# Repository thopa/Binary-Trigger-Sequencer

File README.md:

# Binary-Trigger-Sequencer
8 Channel Eurorack Binary Trigger Sequencer

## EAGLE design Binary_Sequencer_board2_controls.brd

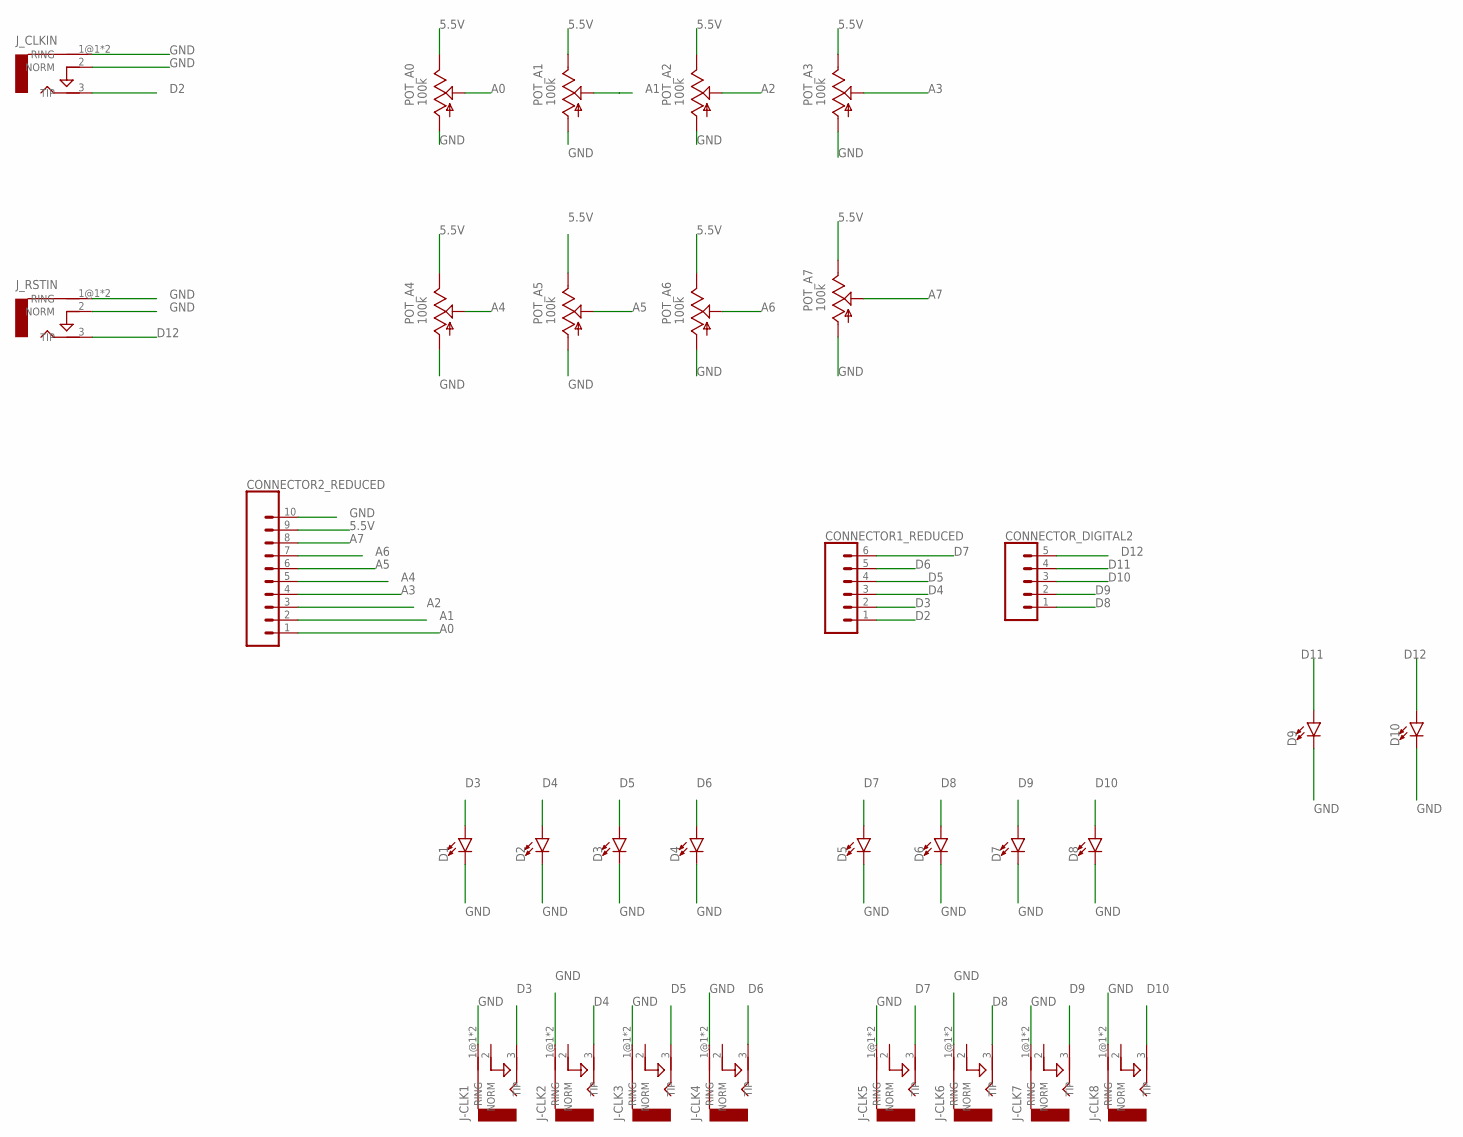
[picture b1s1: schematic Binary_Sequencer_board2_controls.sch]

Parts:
CONNECTOR1_REDUCED: CONN_06LONGPADS; 1X06_LONGPADS
CONNECTOR2_REDUCED: CONN_10_LONGPADS10_LONGPADS; 1X10_LONGPADS
CONNECTOR_DIGITAL2: CONN_05PTH_LONGPADS; 1X05_LONGPADS
D1, D2, D3, D4, D5, D6, D7, D8, D9, D10: LED-3MM-NO_SILK; LED_3MM-NS
J-CLK1, J-CLK2, J-CLK3, J-CLK4, J-CLK5, J-CLK6, J-CLK7, J-CLK8: AUDIO-JACKERTHENVAR; ERTHENVAR-JACK
J_CLKIN: AUDIO-JACKERTHENVAR; ERTHENVAR-JACK
J_RSTIN: AUDIO-JACKERTHENVAR; ERTHENVAR-JACK
POT_A0, POT_A1, POT_A2, POT_A3, POT_A4, POT_A5, POT_A6, POT_A7: 100k; 9MM_SNAP-IN_POT

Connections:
5.5V: CONNECTOR2_REDUCED.9, POT_A0.3 (E), POT_A1.3 (E), POT_A2.3 (E), POT_A3.3 (E), POT_A4.3 (E), POT_A5.3 (E), POT_A6.3 (E), POT_A7.3 (E)
A0: CONNECTOR2_REDUCED.1, POT_A0.2 (S)
A1: CONNECTOR2_REDUCED.2, POT_A1.2 (S)
A2: CONNECTOR2_REDUCED.3, POT_A2.2 (S)
A3: CONNECTOR2_REDUCED.4, POT_A3.2 (S)
A4: CONNECTOR2_REDUCED.5, POT_A4.2 (S)
A5: CONNECTOR2_REDUCED.6, POT_A5.2 (S)
A6: CONNECTOR2_REDUCED.7, POT_A6.2 (S)
A7: CONNECTOR2_REDUCED.8, POT_A7.2 (S)
D2: CONNECTOR1_REDUCED.1, J_CLKIN.3 (TIP)
D3: CONNECTOR1_REDUCED.2, D1.A, J-CLK1.3 (TIP)
D4: CONNECTOR1_REDUCED.3, D2.A, J-CLK2.3 (TIP)
D5: CONNECTOR1_REDUCED.4, D3.A, J-CLK3.3 (TIP)
D6: CONNECTOR1_REDUCED.5, D4.A, J-CLK4.3 (TIP)
D7: CONNECTOR1_REDUCED.6, D5.A, J-CLK5.3 (TIP)
D8: CONNECTOR_DIGITAL2.1, D6.A, J-CLK6.3 (TIP)
D9: CONNECTOR_DIGITAL2.2, D7.A, J-CLK7.3 (TIP)
D10: CONNECTOR_DIGITAL2.3, D8.A, J-CLK8.3 (TIP)
D11: CONNECTOR_DIGITAL2.4, D9.A
D12: CONNECTOR_DIGITAL2.5, D10.A, J_RSTIN.3 (TIP)
GND: CONNECTOR2_REDUCED.10, D1.K (C), D2.K (C), D3.K (C), D4.K (C), D5.K (C), D6.K (C), D7.K (C), D8.K (C), D9.K (C), D10.K (C), J-CLK1.1@1 (RING), J-CLK1.1@2 (RING), J-CLK2.1@1 (RING), J-CLK2.1@2 (RING), J-CLK3.1@1 (RING), J-CLK3.1@2 (RING), J-CLK4.1@1 (RING), J-CLK4.1@2 (RING), J-CLK5.1@1 (RING), J-CLK5.1@2 (RING), J-CLK6.1@1 (RING), J-CLK6.1@2 (RING), J-CLK7.1@1 (RING), J-CLK7.1@2 (RING), J-CLK8.1@1 (RING), J-CLK8.1@2 (RING), J_CLKIN.1@1 (RING), J_CLKIN.1@2 (RING), J_CLKIN.2 (NORM), J_RSTIN.1@1 (RING), J_RSTIN.1@2 (RING), J_RSTIN.2 (NORM), POT_A0.1 (A), POT_A1.1 (A), POT_A2.1 (A), POT_A3.1 (A), POT_A4.1 (A), POT_A5.1 (A), POT_A6.1 (A), POT_A7.1 (A)

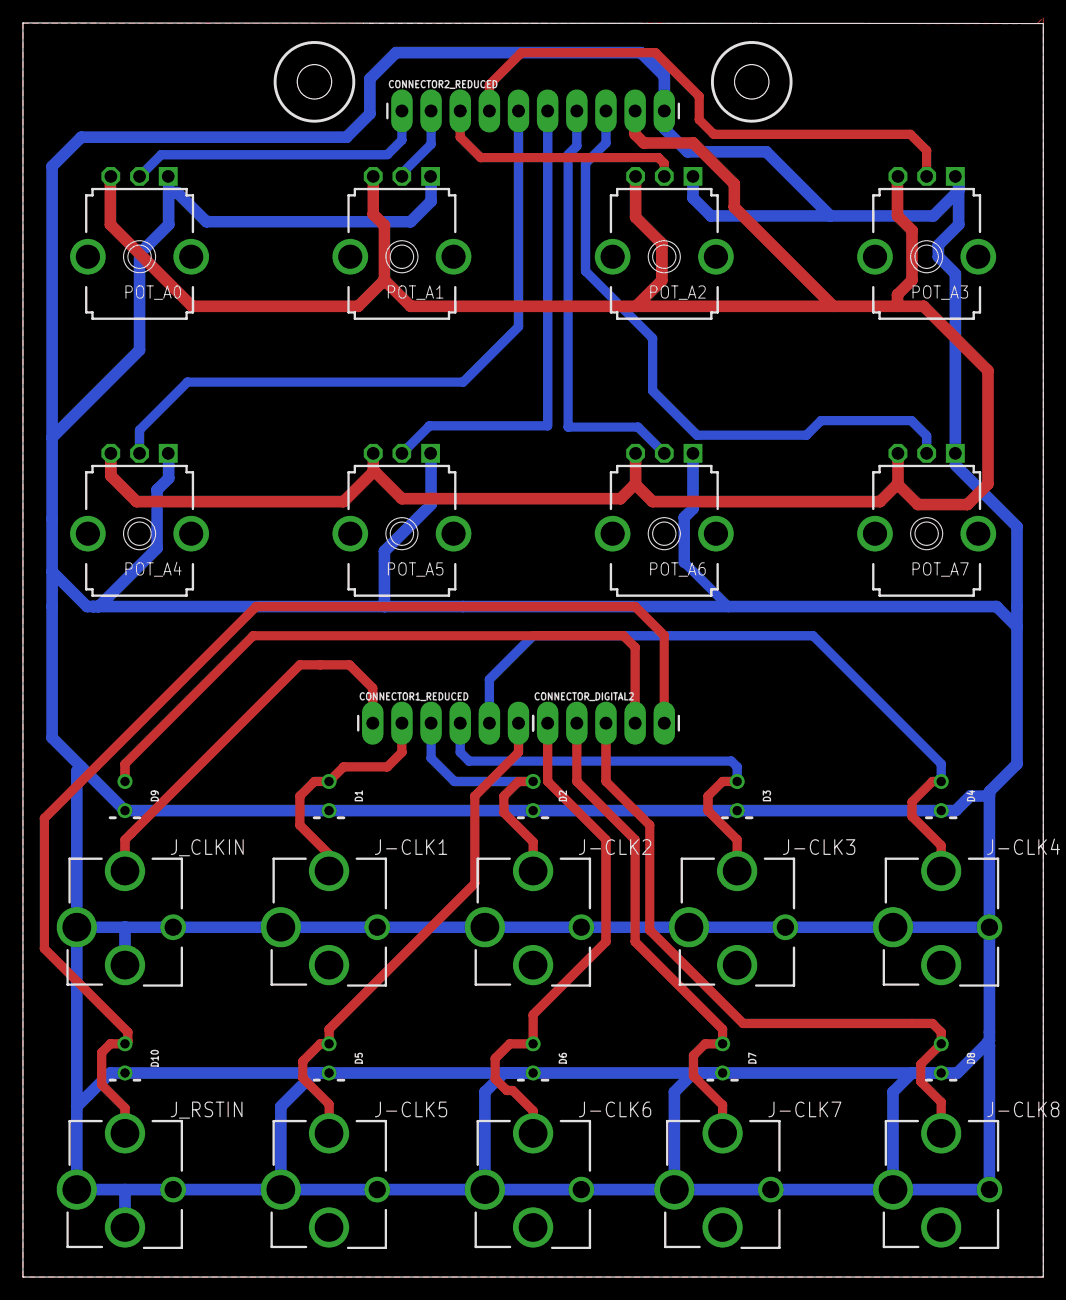
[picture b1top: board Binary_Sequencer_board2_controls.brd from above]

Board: 2 copper layers, 88.9 x 109.3 mm, 33 parts (0 on the bottom side), 21 nets.

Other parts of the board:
H1, H2: DRIL-3

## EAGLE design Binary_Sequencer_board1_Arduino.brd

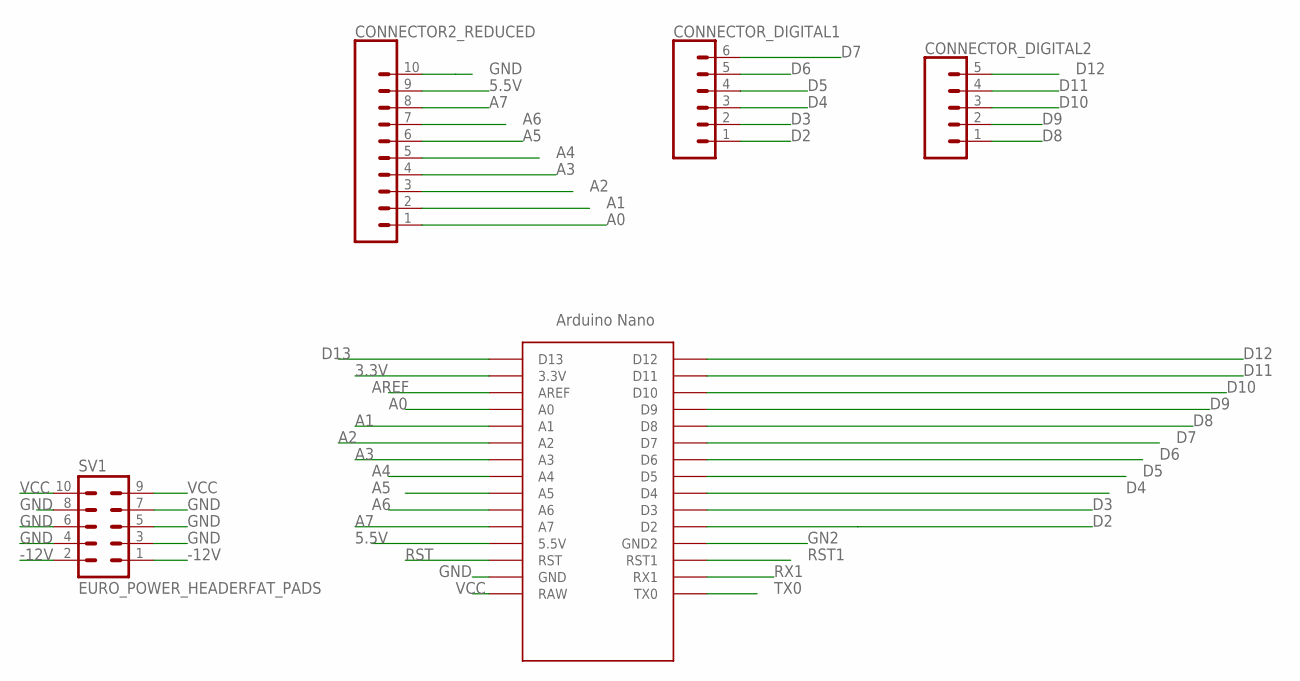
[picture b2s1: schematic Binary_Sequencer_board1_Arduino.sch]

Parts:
CONNECTOR2_REDUCED: CONN_10_LONGPADS10_LONGPADS; 1X10_LONGPADS
CONNECTOR_DIGITAL1: CONN_06LONGPADS; 1X06_LONGPADS
CONNECTOR_DIGITAL2: CONN_05PTH_LONGPADS; 1X05_LONGPADS
SV1: EURO_POWER_HEADERFAT_PADS; EURO_PWR_HEADER_FAT
U$1: NANO

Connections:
3.3V: U$1.3.3V
5.5V: CONNECTOR2_REDUCED.9, U$1.5V (5.5V)
-12V: SV1.1, SV1.2
A0: CONNECTOR2_REDUCED.1, U$1.A0
A1: CONNECTOR2_REDUCED.2, U$1.A1
A2: CONNECTOR2_REDUCED.3, U$1.A2
A3: CONNECTOR2_REDUCED.4, U$1.A3
A4: CONNECTOR2_REDUCED.5, U$1.A4
A5: CONNECTOR2_REDUCED.6, U$1.A5
A6: CONNECTOR2_REDUCED.7, U$1.A6
A7: CONNECTOR2_REDUCED.8, U$1.A7
AREF: U$1.AREF
D2: CONNECTOR_DIGITAL1.1, U$1.D2
D3: CONNECTOR_DIGITAL1.2, U$1.D3
D4: CONNECTOR_DIGITAL1.3, U$1.D4
D5: CONNECTOR_DIGITAL1.4, U$1.D5
D6: CONNECTOR_DIGITAL1.5, U$1.D6
D7: CONNECTOR_DIGITAL1.6, U$1.D7
D8: CONNECTOR_DIGITAL2.1, U$1.D8
D9: CONNECTOR_DIGITAL2.2, U$1.D9
D10: CONNECTOR_DIGITAL2.3, U$1.D10
D11: CONNECTOR_DIGITAL2.4, U$1.D11
D12: CONNECTOR_DIGITAL2.5, U$1.D12
D13: U$1.D13
GN2: U$1.GND1 (GND2)
GND: CONNECTOR2_REDUCED.10, SV1.3, SV1.4, SV1.5, SV1.6, SV1.7, SV1.8, U$1.GND
RST: U$1.RST
RST1: U$1.RST1
RX1: U$1.RX1
TX0: U$1.TX0
VCC: SV1.9, SV1.10, U$1.RAW

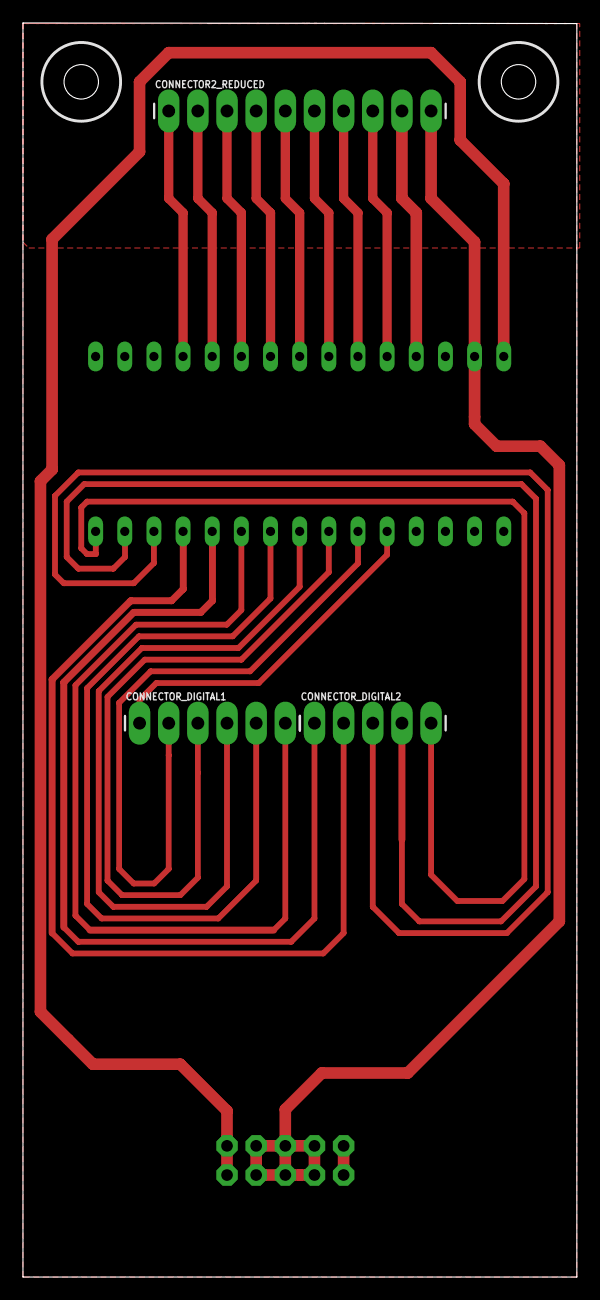
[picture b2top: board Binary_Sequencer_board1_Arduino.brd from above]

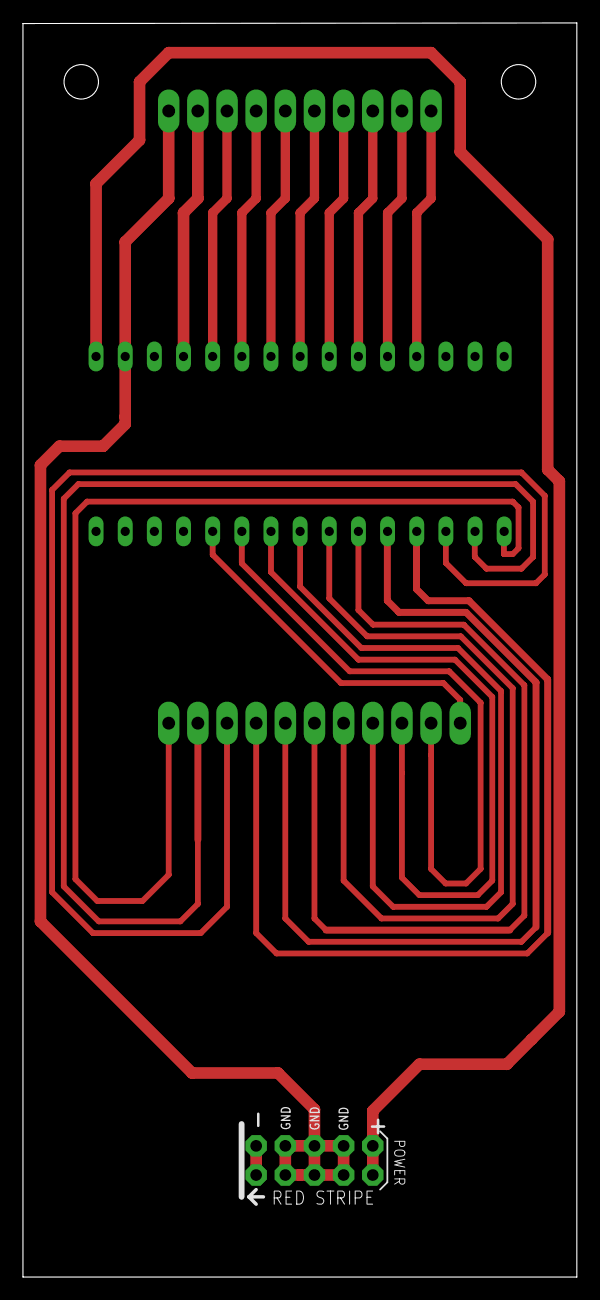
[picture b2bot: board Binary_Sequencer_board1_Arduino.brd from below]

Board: 2 copper layers, 48.3 x 109.3 mm, 7 parts (2 on the bottom side), 23 nets.

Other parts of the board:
H1, H2: DRIL-3

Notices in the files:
parts and their libraries:
SparkFun-Connectors: Licensing: Creative Commons ShareAlike 4.0 International - https://creativecommons.org/licenses/by-sa/4.0
